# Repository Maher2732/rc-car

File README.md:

# RC Car

An autonomous-assist RC car built on three networked computers. You drive it with an Xbox controller paired straight to an ESP32 over Bluetooth. A Raspberry Pi watches the road with a 360° lidar and steps in when you're about to hit something. A second ESP32 watches the battery and runs a 3.5" dashboard display. Both ESP32s live on one custom mainboard (see [`PCB/`](PCB/)). All three talk over a CAN bus, the same kind of network real cars use.

```
                    Bluetooth (Bluepad32)
  Xbox controller  ─────────────────────►  ┌──────────────────────┐ ──PWM──► Steering servo
                                           │  DRIVE NODE (ESP32)  │
                                           │  steering + motor    │ ──PWM──► BTS7960 ──► Motor
                                           └──────────┬───────────┘
                                                      │
  ════════════════════════════ CAN bus, 500 kbit/s ═══╪══════════════════════════════
            │                                         │
  ┌─────────┴──────────────┐            ┌─────────────┴─────────┐
  │  RASPBERRY PI          │            │  TELEMETRY NODE       │ ──► 3.5" ILI9488 display
  │  lidar obstacle        │            │  (ESP32)              │ ◄── Battery voltage divider
  │  avoidance             │            │  battery + dashboard  │
  └─────────┬──────────────┘            └───────────────────────┘
            ▲
         RPLidar
```

## How It Works

1. **You drive.** The drive node reads the controller over Bluetooth and drives the steering servo and the motor through a BTS7960 H-bridge. No PC and no cables.
2. **The telemetry node reports.** It reads the battery voltage and broadcasts it on the CAN bus, and its display shows whether the controller is connected, battery %, and the nearest object the lidar sees.
3. **The Pi watches.** Every lidar scan, it looks for anything inside the corridor the car is about to drive through. It works out a stopping distance from the car's speed. There's no wheel-speed sensor, so it assumes a safe upper bound.
4. **The Pi corrects.** It sends a correction addressed to the drive node (CAN ID `0x100`) at 20 Hz: a throttle limit, a steering nudge toward the side with more room, or a full forward block. The drive node merges this with your input. You stay in control, and the car just won't let you drive into a wall.

## Engineering Highlights

- **Fail-safe by default.** Every link has a timeout, and losing one makes the car *more* cautious, never less:

  | Fault | Response |
  |-------|----------|
  | Controller disconnects | Neutral throttle, centered steering |
  | Pi stops sending (crash, unplugged, booting) | Forward throttle capped at 50% |
  | Lidar stops producing scans | Pi caps throttle at 30% |
  | Battery critically low | Throttle capped at 30%, latched until reboot |
  | CAN controller goes bus-off | Automatic recovery |

- **Speed-aware braking.** Stop distance = buffer + speed × reaction time + speed² / (2 × deceleration), with hysteresis so the block doesn't chatter at the threshold.
- **Shared protocol, checked in CI.** The CAN message layout lives in one C header. A Python test parses that header and fails if the Pi's copy drifts.
- **Pure, testable logic.** The rules for merging driver input with corrections (`drive_logic.c`) and the avoidance algorithm (`avoidance.py`) contain no hardware calls. The avoidance code has unit tests.
- **Drivetrain protection.** Throttle can only rise at a limited rate, which protects the 3D-printed differential from shock loads. Letting off and braking still take effect instantly.
- **Motor protection.** The H-bridge brakes for 250 ms before it reverses, so a full-speed forward-to-reverse flip never slams the spinning motor into reverse (a large current spike through the driver and the 3D-printed gears). Drag brake holds the crawler on slopes and stops it fast when the Pi cuts throttle. 20 kHz PWM keeps the motor quiet.
- **Haptic feedback.** The controller rumbles when the Pi blocks forward motion.
- **Real-time structure.** On the drive node, Bluetooth runs on core 0 and the 50 Hz control loop is pinned to core 1.

## Controls

| Input | Action |
|-------|--------|
| Left stick X | Steering |
| Right trigger | Throttle |
| Left trigger | Brake / reverse |
| Y | Toggle slow (40%) / fast (100%) mode |
| D-pad left / right | Steering trim (±1° per press) |

**Pairing:** power on the drive node, then hold the pair button on top of the Xbox controller until the logo flashes quickly. After the first pairing, the controller reconnects automatically. Only one controller can connect at a time. To forget the pairing, run `idf.py erase-flash` and reflash.

## Hardware

| Part | Notes |
|------|-------|
| 2× ESP32 dev board | Classic ESP32 (needs Bluetooth Classic + BLE for Xbox controllers) |
| Raspberry Pi | Any model with SPI; runs Raspberry Pi OS |
| 3× CAN transceiver | SN65HVD230 for each ESP32; MCP2515 CAN HAT for the Pi |
| Slamtec RPLIDAR A1M8 | 360°, 12 m range, USB to the Pi |
| 270° steering servo | 500–2500 µs pulse range |
| INJORA 540 35T brushed motor | Crawler motor, runs straight off the 2S pack |
| Treedix BTS7960 (43 A) | H-bridge motor driver, 20 kHz PWM |
| 5–6 V 7 A UBEC | Set to 5 V; powers the servo and both ESP32s from the LiPo (the BTS7960 has no BEC) |
| 3.5" ILI9488 SPI display (480×320, touch) | Dashboard on the telemetry ESP32 |
| RC Car Mainboard | Custom PCB carrying both ESP32s, CAN, power and connectors ([`PCB/`](PCB/)) |
| Zeee 2S 7.4 V 2200 mAh LiPo | Voltage measured through a 100k / 33k divider |
| Xbox Wireless Controller | Paired over Bluetooth |

### Wiring

**Drive node**

| ESP32 pin | Connects to |
|-----------|-------------|
| GPIO 18 | Steering servo signal |
| GPIO 25 | BTS7960 RPWM (forward) |
| GPIO 26 | BTS7960 LPWM (reverse) |
| GPIO 33 | BTS7960 R_EN + L_EN (tied together) |
| 3V3 | BTS7960 VCC (logic supply, see below) |
| GPIO 4 | CAN transceiver TX |
| GPIO 5 | CAN transceiver RX |

**Telemetry node**

| ESP32 pin | Connects to |
|-----------|-------------|
| GPIO 34 | Battery divider midpoint |
| GPIO 18 / 23 / 19 | Display SPI clock / MOSI / MISO (touch) |
| GPIO 13 / 21 / 22 | Display CS / DC / RESET |
| GPIO 32 | Display backlight (low = on, via a MOSFET on the mainboard) |
| GPIO 14 / 35 | Touch CS / IRQ (wired, not used yet) |
| GPIO 4 | CAN transceiver TX |
| GPIO 5 | CAN transceiver RX |

CAN pins default to GPIO 4 / 5 and can be changed in menuconfig.

**CAN bus:** connect CANH to CANH and CANL to CANL on all three transceivers, put a **120 Ω terminator at each end** of the bus, and share a common ground. Power the servo from a separate 5–6 V UBEC, not from the ESP32.

**BTS7960:** connect B+ / B− to the LiPo and M+ / M− to the motor. Power its **VCC from the ESP32's 3.3 V**, not 5 V. Its input buffer then treats the ESP32's 3.3 V signals as a clean logic high; at 5 V they're borderline. Leave R_IS / L_IS unconnected.

### Power

```
                ┌──► BTS7960 B+/B− ──► Motor
2S LiPo 7.4 V ──┼──► UBEC (5 V) ──┬──► Steering servo (+/−)
                │                 ├──► Drive ESP32 (5V/VIN pin)
                │                 └──► Telemetry ESP32 (5V/VIN pin)
                └──► Telemetry battery divider (100k / 33k)

Raspberry Pi: its own 5 V 3 A+ supply (power bank or a second buck converter)
```

- **Set the UBEC to 5 V.** The ESP32 boards expect 5 V on their 5V/VIN pin, and most hobby servos are happy at 5 V. If your servo is rated for 6 V you'll get a bit more speed and torque at 6 V, but then power the ESP32s separately.
- **Keep the Raspberry Pi off the servo's supply.** A servo straining under load pulls amps in bursts and drags the rail down, which can make the Pi brown out and corrupt its SD card. A Pi 4 alone wants 5 V / 3 A.
- **Common ground.** Every negative wire (LiPo, UBEC, BTS7960, both ESP32s, Pi, CAN transceivers) must connect, or PWM and CAN signals have no reference.
- **Don't plug in USB and the UBEC at once** on an ESP32 unless your board has a protection diode on its 5V pin.

## CAN Protocol

Classic CAN at 500 kbit/s, 11-bit IDs, little-endian. Full definition: [`rc_can_protocol.h`](firmware/components/rc_common/include/rc_can_protocol.h).

| ID | From → To | Rate | Contents |
|----|-----------|------|----------|
| `0x100` | Pi → Drive (+ telemetry display) | 20 Hz | Steering offset, throttle limit, block-forward flag, nearest obstacle in the path and in any direction |
| `0x200` | Drive → all | 20 Hz | Steering angle, throttle, status flags |
| `0x300` | (reserved) | | Wheel speed, for a future speed sensor |
| `0x301` | Telemetry → all | 5 Hz | Pack voltage, % charge, low/critical flags |

Each message carries a rolling counter, and receivers treat a message older than 300 ms as "node offline".

## Getting Started

### 1. Clone with submodules

Bluepad32 and BTstack are git submodules:

```bash
git clone --recursive https://github.com/Maher2732/rc-car.git
```

If you already cloned without `--recursive`:

```bash
git submodule update --init --recursive
```

### 2. Flash the ESP32s

Requires [ESP-IDF](https://docs.espressif.com/projects/esp-idf/) v6.1. Every ESP32 runs the same firmware project; you pick what each board does in menuconfig:

```bash
cd firmware
idf.py menuconfig
```

Go to **RC Car Configuration → Board role** and choose one:

| Role | What it does |
|------|--------------|
| Drive node *(default)* | Xbox controller over Bluetooth, steering servo, BTS7960 motor driver, applies Pi corrections |
| Telemetry node | Battery monitoring and the dashboard display |
| CAN sender | Test tool: sends a frame every second |
| CAN receiver | Test tool: listen-only, prints every frame on the bus |

Then build and flash:

```bash
idf.py build flash monitor
```

Changing role rewrites `sdkconfig`, so flash one board, change the role, and flash the next. The CAN sender/receiver roles are handy for checking the wiring and termination before running the real nodes.

Tune pins, steering limits, speed modes and battery settings in `main/drive/config.h` and `main/telemetry/config.h`.

### 3. Set up the Raspberry Pi

Enable the CAN HAT in `/boot/firmware/config.txt`. Match `oscillator` to the crystal on your HAT:

```
dtparam=spi=on
dtoverlay=mcp2515-can0,oscillator=8000000,interrupt=25
```

Bring `can0` up at boot and install the code:

```bash
sudo cp pi/deploy/can0.network /etc/systemd/network/80-can0.network
sudo systemctl enable --now systemd-networkd
cd pi && python3 -m venv .venv && .venv/bin/pip install -r requirements.txt
```

Run it by hand:

```bash
.venv/bin/python -m rc_pi.main --lidar-port /dev/ttyUSB0 --verbose
```

Or install it as a service that starts at boot:

```bash
sudo cp deploy/rc-pi.service /etc/systemd/system/ && sudo systemctl enable --now rc-pi
```

Tune car width, braking deceleration and lidar mounting angle in [`pi/rc_pi/config.py`](pi/rc_pi/config.py).

### 4. Run the tests

```bash
cd pi && python -m unittest discover -s tests -t . -v
```

GitHub Actions runs these tests and builds the firmware in every board role on every push.

## Project Structure

```
firmware/                      # One ESP-IDF project, board role chosen in menuconfig
├── main/
│   ├── main.c                 #   Runs the selected role
│   ├── Kconfig.projbuild      #   Board role + CAN pins
│   ├── drive/                 #   Role: drive node
│   │   ├── gamepad.c          #     Bluepad32 platform: Xbox controller input
│   │   ├── drive_logic.c      #     Merges driver input with Pi corrections and limits
│   │   ├── actuators.c        #     Servo PWM + BTS7960 motor driver
│   │   └── config.h           #     Pins and tuning
│   ├── telemetry/             #   Role: telemetry node
│   │   ├── display.c          #     ILI9488 driver + 5x7 font
│   │   ├── telemetry_node.c   #     Battery messages + dashboard screen
│   │   ├── battery.c          #     Calibrated ADC, LiPo charge estimate, low/critical flags
│   │   └── config.h
│   ├── can_sender.c           #   Role: CAN test sender
│   └── can_receiver.c         #   Role: CAN test receiver
├── components/rc_common/      # Shared CAN driver + protocol header
└── external/bluepad32/        # Submodule
pi/
├── rc_pi/
│   ├── avoidance.py           # Obstacle detection + correction logic
│   ├── lidar.py               # Background RPLidar reader with auto-reconnect
│   ├── can_link.py            # CAN send/receive
│   ├── protocol.py            # Python mirror of the CAN protocol
│   └── main.py                # 20 Hz main loop
├── tests/                     # Unit tests (avoidance, protocol sync, CAN link)
└── deploy/                    # systemd service + CAN interface config
PCB/
├── generator/                 # Python that generates the KiCad schematic + board
├── mainboard/                 # KiCad 10 project
├── fab/                       # Gerbers, BOM, pick-and-place for PCBWay
└── images/                    # 3D renders
```

## Roadmap

- [ ] Block reverse when the lidar sees something behind the car
- [ ] Log CAN traffic on the Pi for replay and tuning
- [ ] Use the display's touch panel (speed mode, steering trim)
- [ ] Wheel-speed sensor for tighter braking distances

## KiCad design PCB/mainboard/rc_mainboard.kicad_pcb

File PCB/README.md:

# RC Car Mainboard

One board that replaces the wiring nest: both ESP32s, CAN, power, and every connector the car needs. The Raspberry Pi stays on its own board and joins over the CAN connector.

| | |
|---|---|
| Size | **130 × 100 mm** (5.1 × 3.9 in), 3 mm corner radius |
| Layers | 2, 1.6 mm FR-4 |
| Copper | 2 oz recommended (battery → motor path carries motor current) |
| Smallest features | 0.15 mm traces, 0.2 mm holes (PCBWay standard process) |

## What's on it

| Block | Parts |
|-------|-------|
| Power input | XT60 battery in, 30 A blade fuse, reverse-polarity MOSFET, soft on/off switch (MOSFET + edge slide switch), XT60 out to the BTS7960 |
| Servo supply | TPS54560B, 5 V / 5 A, own polyfuse |
| Logic supply | AP63205 5 V buck, OR-ed with both USB ports, AMS1117 3.3 V |
| Drive ESP32 | ESP32-WROOM-32E, USB-C + CH340C with auto-program, servo header, 8-pin BTS7960 header |
| Telemetry ESP32 | ESP32-WROOM-32E, USB-C + CH340C, battery voltage divider, 14-pin display socket |
| CAN | Two SN65HVD230 on board, split 120 Ω termination (cut JP1 to disable), TVS protection, JST-XH to the Pi |

### Connectors

| Ref | Connector | Goes to |
|-----|-----------|---------|
| J1 | XT60 male | 2S LiPo |
| J2 | XT60 female | BTS7960 B+ / B− |
| SW1 | Slide switch (board edge) | Turns the whole car on and off |
| J6 | 1×8 header, 2.54 mm | BTS7960 control header, pin for pin (straight ribbon) |
| J7 | 1×3 header, 2.54 mm | Steering servo (S, +, −) |
| J8 | 1×14 socket, 2.54 mm | 3.5" ILI9488 display, pin for pin |
| J5 | JST-XH 3-pin | CAN to the Raspberry Pi (H, L, GND) |
| J3 / J4 | USB-C | Flash / power the drive / telemetry ESP32 |

## Ordering from PCBWay

Upload `fab/rc_mainboard_gerbers.zip` at pcbway.com → PCB Instant Quote → Quick-order PCB. Settings:

| Option | Value |
|--------|-------|
| Layers | 2 |
| Size | 130 × 100 mm |
| Thickness | 1.6 mm |
| Min track / spacing | 6/6 mil (0.15 mm) |
| Min hole | 0.2 mm |
| Outer copper | **2 oz** |
| Surface finish | HASL lead-free (or ENIG) |

**Assembly (optional):** choose PCB Assembly and upload `fab/rc_mainboard_bom.csv` and `fab/rc_mainboard_centroid.csv` with the Gerbers. The BOM lists a manufacturer part number for every IC, so PCBWay can source them. Through-hole parts (XT60s, fuse holder, switch, headers) are marked THT; they're easy to hand-solder if you'd rather save on assembly.

The ESP32 modules ship blank. Flash each one over its own USB-C port; pick the role in `idf.py menuconfig` (drive on the board marked USB DRIVE, telemetry on USB TELEMETRY).

## Before you power it up

1. Inspect the battery path (J1 → F1 → Q1 → Q2 → J2) for solder bridges.
2. Plug in USB only first: the green power LED should light and both ESP32s should enumerate.
3. Then connect the battery with SW1 off, and turn SW1 on.
4. Check the servo rail (J7 pin 2) reads about 5.0 V before plugging the servo in.

## Design notes

- **Servo supply compensation** uses values for a 5 V / 5 A output at ~490 kHz. They're a reasonable starting point; confirm with TI's WEBENCH or the TPS54560B datasheet before ordering a large batch.
- **Antennas** overhang the top edge with a copper keep-out underneath; mount the board so nothing metal sits right above them.
- **Display backlight** is switched by Q7: IO32 low = on (the firmware does this).
- **Touch panel** is wired (SPI shared with the display, IO14 CS, IO35 IRQ) but the firmware doesn't use it yet.

## Regenerating

Everything is generated from [`generator/design.py`](generator/design.py), one list of every part and connection. Edit that, not the KiCad files.

```bash
cd PCB/generator
python gen_sch.py                      # schematic
<kicad>/bin/python.exe route.py        # board + autoroute (needs Freerouting + Java 25)
<kicad>/bin/python.exe export.py       # PCBWay files + renders
```

`<kicad>` is the KiCad 10 install folder; `route.py` reads `FREEROUTING_JAR` and `JAVA` from the environment.

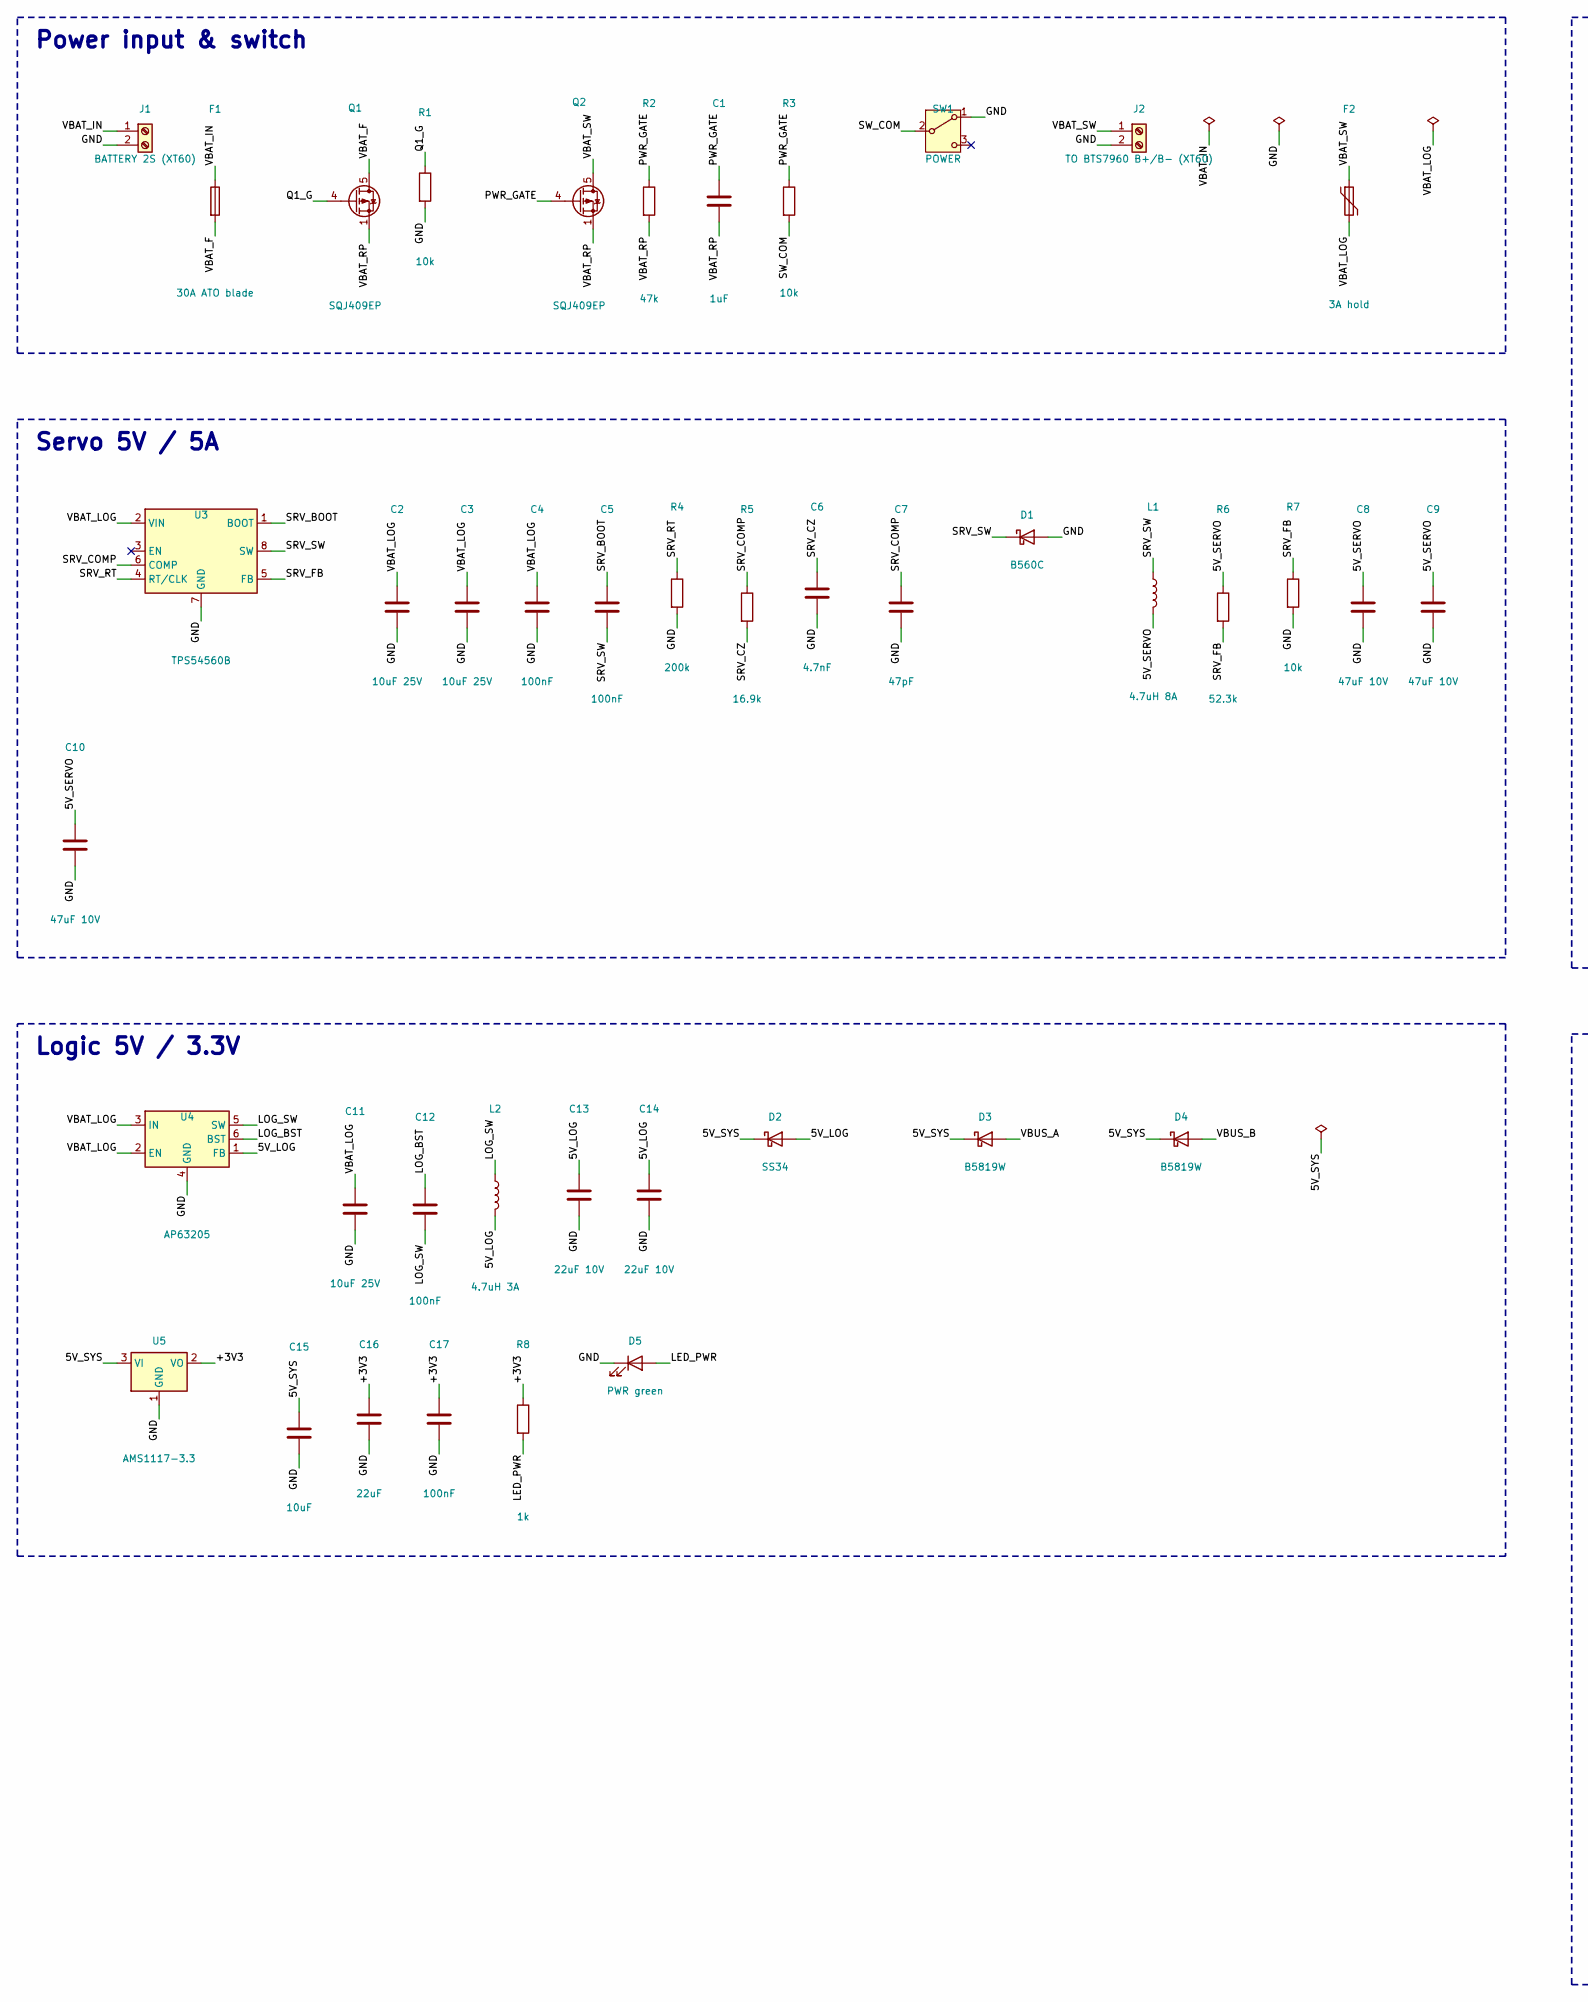
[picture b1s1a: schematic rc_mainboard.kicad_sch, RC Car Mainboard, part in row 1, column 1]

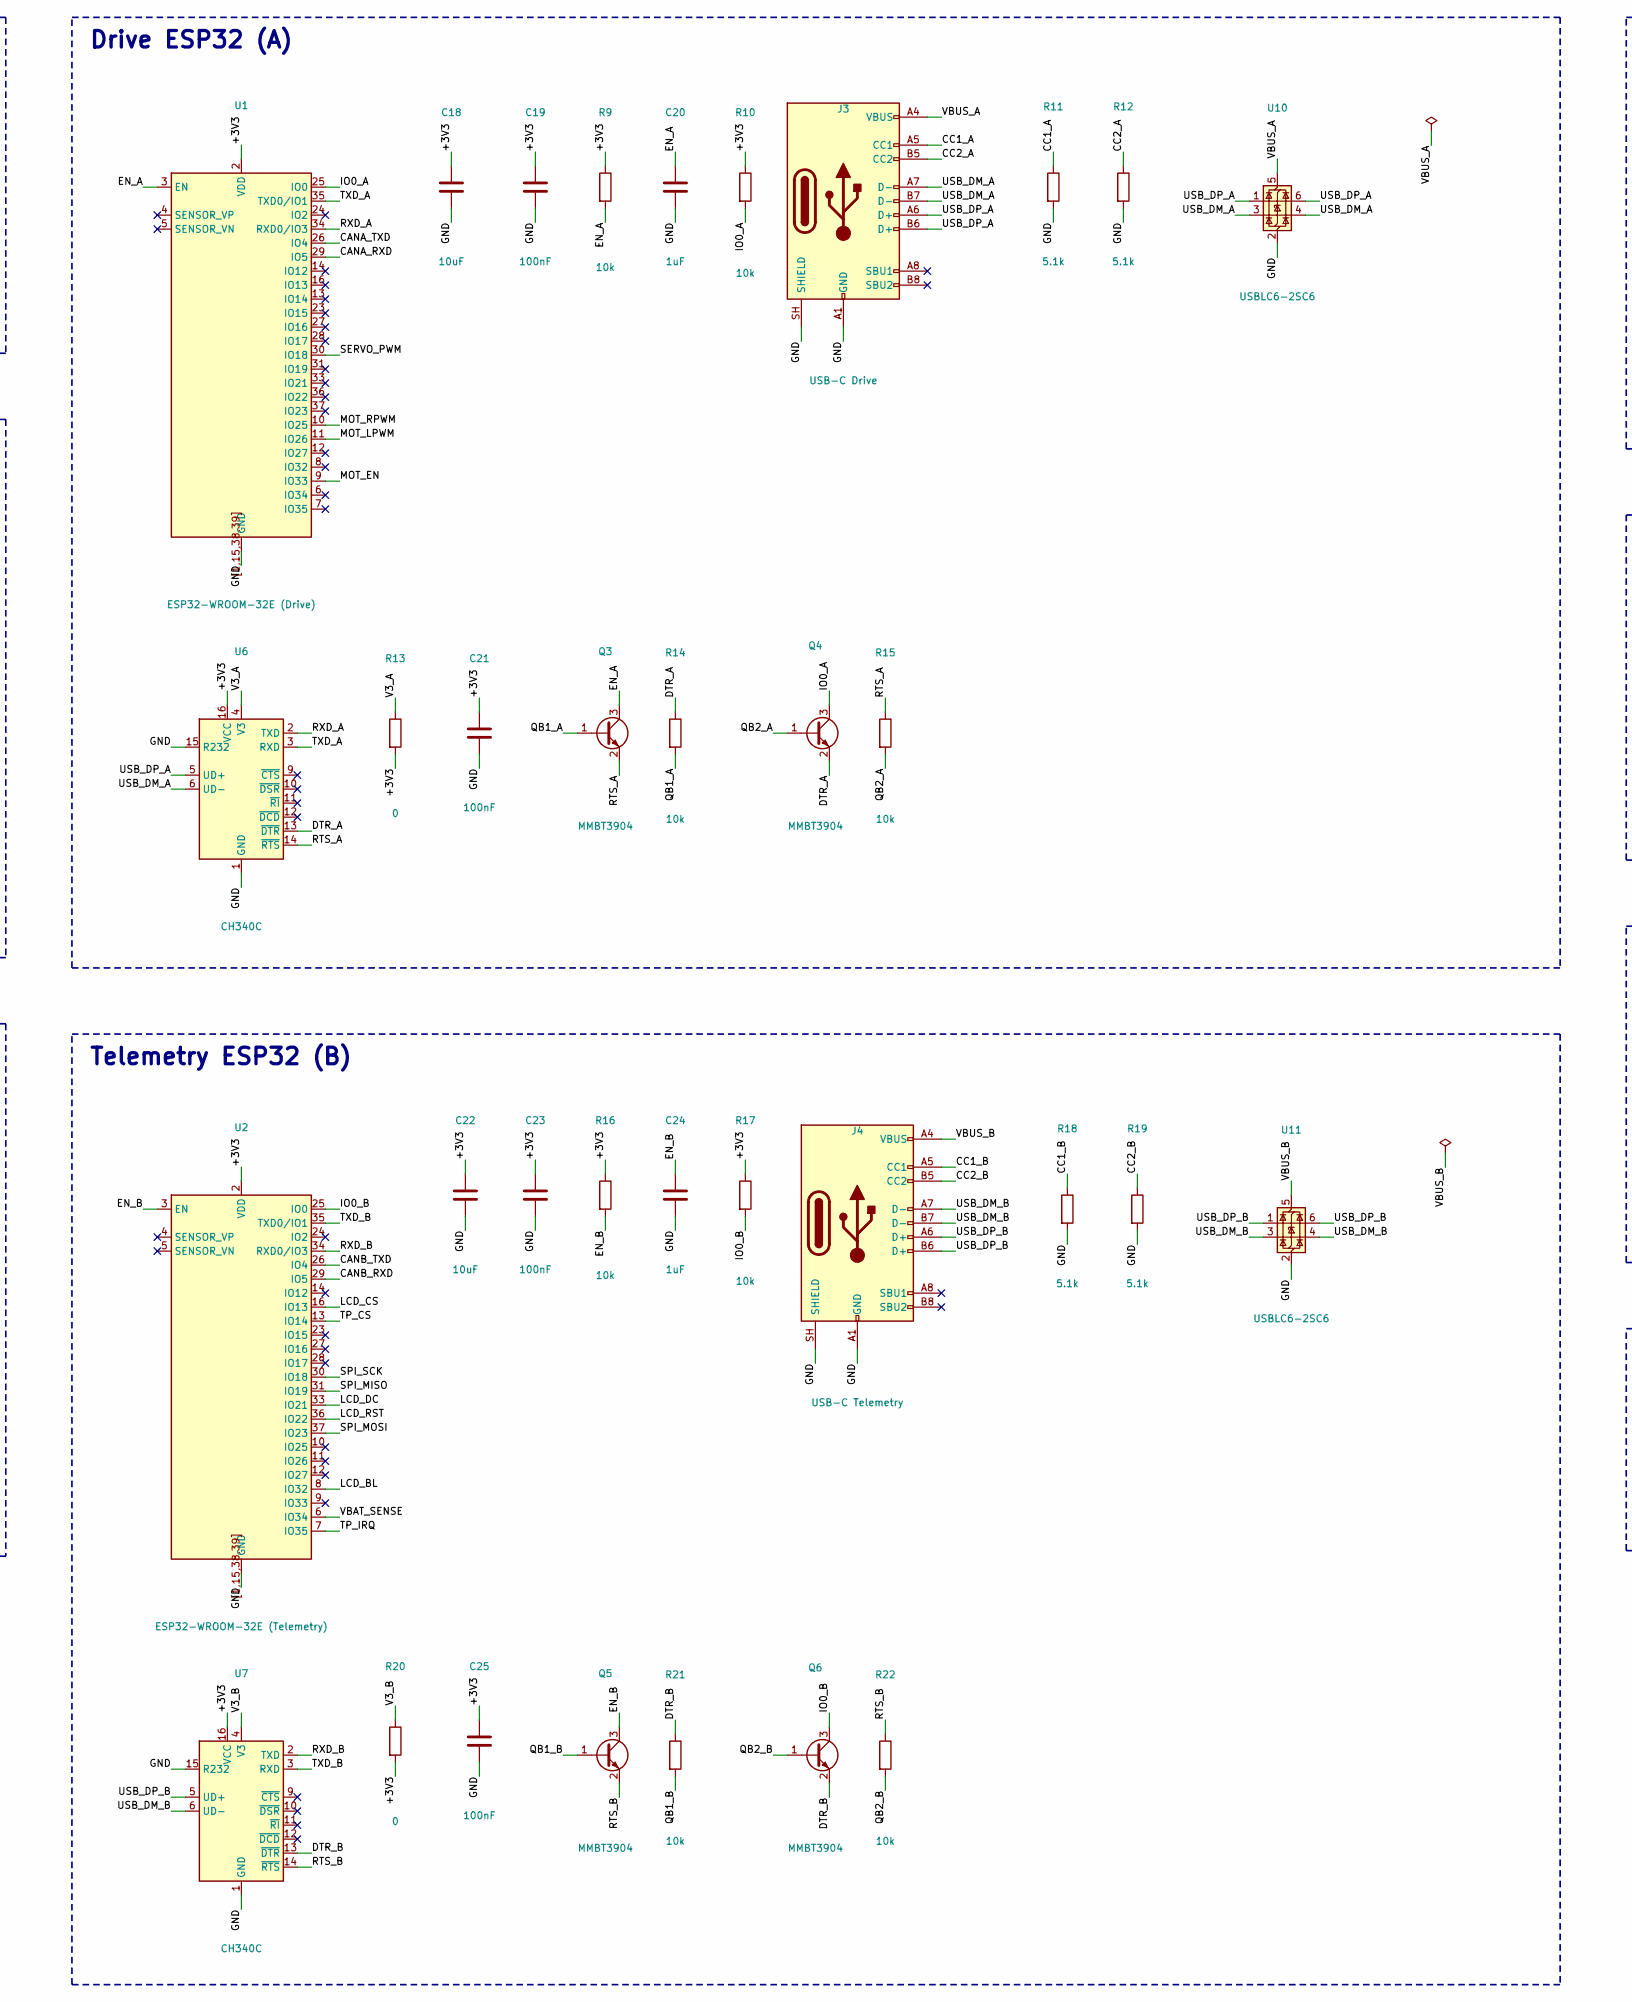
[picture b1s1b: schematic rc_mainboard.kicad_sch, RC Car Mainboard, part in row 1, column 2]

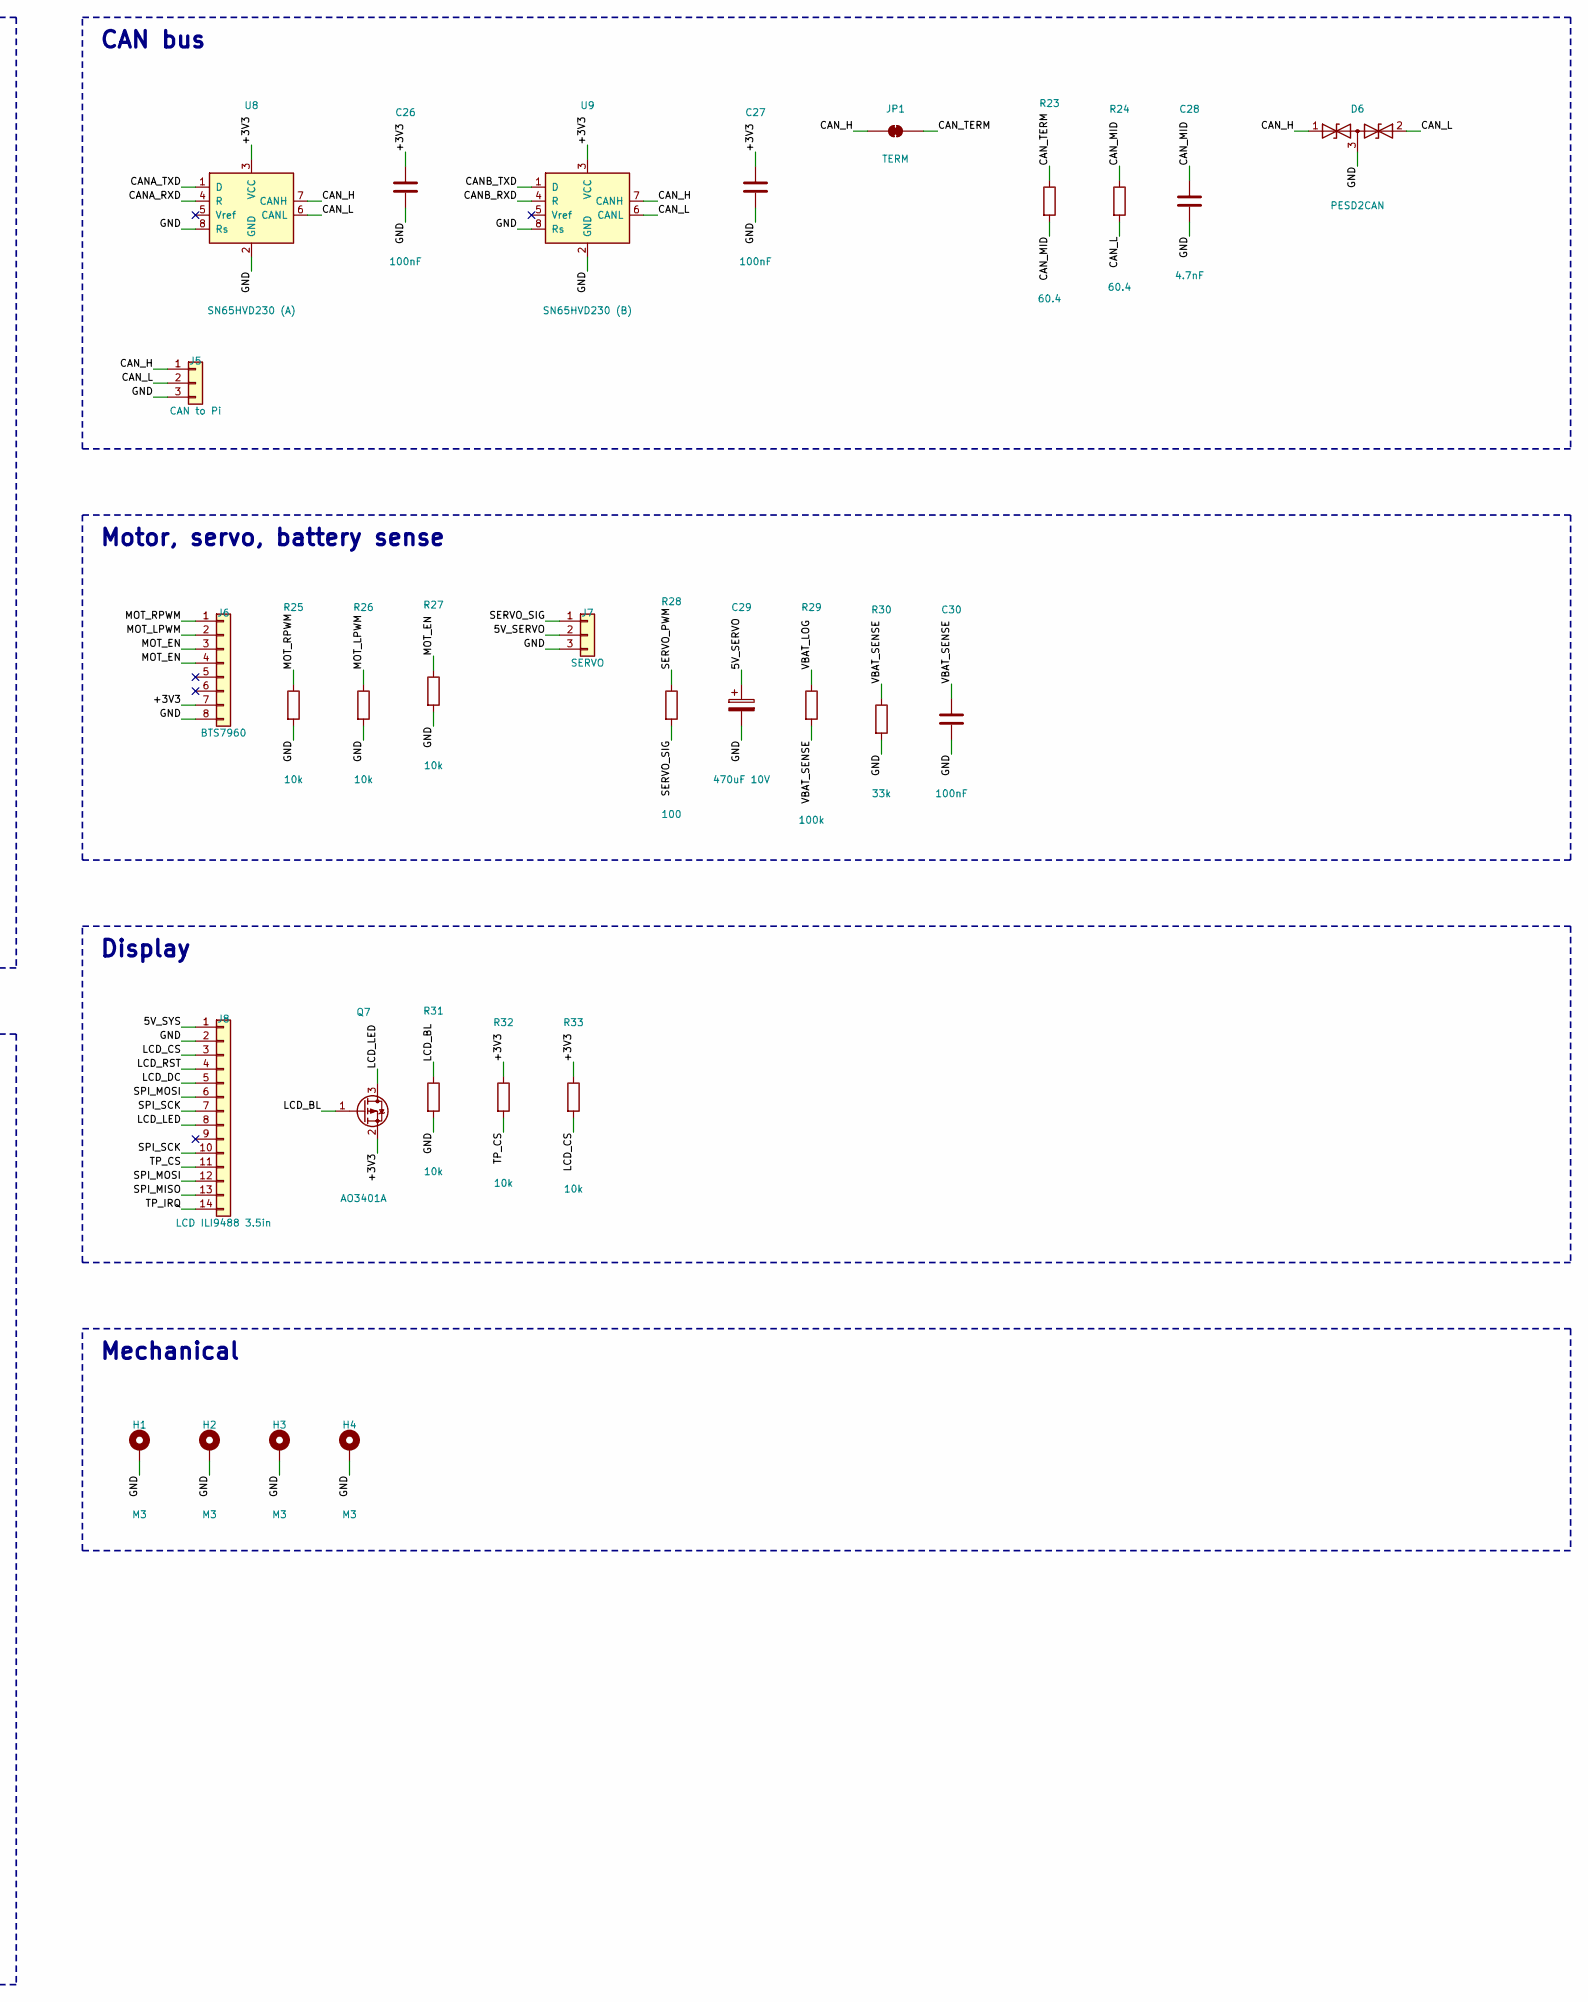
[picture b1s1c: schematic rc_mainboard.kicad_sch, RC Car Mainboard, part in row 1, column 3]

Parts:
C1: 1uF; C_0805_2012Metric
C2, C3, C11: 10uF 25V; C_1206_3216Metric
C4, C5, C12, C17, C19, C21, C23, C25, C26, C27, C30: 100nF; C_0603_1608Metric
C6, C28: 4.7nF; C_0603_1608Metric
C7: 47pF; C_0603_1608Metric
C8, C9, C10: 47uF 10V; C_1206_3216Metric
C13, C14: 22uF 10V; C_0805_2012Metric
C15, C18, C22: 10uF; C_0805_2012Metric
C16: 22uF; C_0805_2012Metric
C20, C24: 1uF; C_0603_1608Metric
C29: 470uF 10V; CP_Elec_8x10
D1: B560C; D_SMC; MPN B560C-13-F
D2: SS34; D_SMA; MPN SS34
D3, D4: B5819W; D_SOD-123; MPN B5819W
D5: PWR green; LED_0603_1608Metric
D6: PESD2CAN; SOT-23; MPN PESD2CAN,215
F1: 30A ATO blade; FuseHolder_Blade_ATO_Littelfuse_FLR_178.6165; MPN Littelfuse 178.6165
F2: 3A hold; Fuse_2920_7451Metric; MPN PTC 2920 3A hold
H1, H2, H3, H4: M3; MountingHole_3.2mm_M3_Pad_Via
J1: BATTERY 2S (XT60); AMASS_XT60PW-M_1x02_P7.20mm_Horizontal; MPN XT60PW-M
J2: TO BTS7960 B+/B- (XT60); AMASS_XT60PW-F_1x02_P7.20mm_Horizontal; MPN XT60PW-F
J3: USB-C Drive; USB_C_Receptacle_HRO_TYPE-C-31-M-12; MPN TYPE-C-31-M-12
J4: USB-C Telemetry; USB_C_Receptacle_HRO_TYPE-C-31-M-12; MPN TYPE-C-31-M-12
J5: CAN to Pi; JST_XH_B3B-XH-A_1x03_P2.50mm_Vertical; MPN B3B-XH-A
J6: BTS7960; PinHeader_1x08_P2.54mm_Vertical
J7: SERVO; PinHeader_1x03_P2.54mm_Vertical
J8: LCD ILI9488 3.5in; PinSocket_1x14_P2.54mm_Vertical
JP1: TERM; SolderJumper-2_P1.3mm_Bridged_RoundedPad1.0x1.5mm
L1: 4.7uH 8A; L_Bourns_SRP1038C_10.0x10.0mm; MPN SRP1038C-4R7M
L2: 4.7uH 3A; L_Bourns-SRN4018; MPN SRN4018-4R7M
Q1, Q2: SQJ409EP; PowerPAK_SO-8L_Single; MPN SQJ409EP-T1_GE3
Q3, Q4, Q5, Q6: MMBT3904; SOT-23; MPN MMBT3904
Q7: AO3401A; SOT-23; MPN AO3401A
R1, R3, R7, R9, R10, R14, R15, R16, R17, R21, R22, R25, R26, R27, R31, R32, R33: 10k; R_0603_1608Metric
R2: 47k; R_0603_1608Metric
R4: 200k; R_0603_1608Metric
R5: 16.9k; R_0603_1608Metric
R6: 52.3k; R_0603_1608Metric
R8: 1k; R_0603_1608Metric
R11, R12, R18, R19: 5.1k; R_0603_1608Metric
R13, R20: 0; R_0603_1608Metric
R23, R24: 60.4; R_0603_1608Metric
R28: 100; R_0603_1608Metric
R29: 100k; R_0603_1608Metric
R30: 33k; R_0603_1608Metric
SW1: POWER; SW_Slide_SPDT_Angled_CK_OS102011MA1Q; MPN OS102011MA1QN1
U1: ESP32-WROOM-32E (Drive); ESP32-WROOM-32E; MPN ESP32-WROOM-32E-N4
U2: ESP32-WROOM-32E (Telemetry); ESP32-WROOM-32E; MPN ESP32-WROOM-32E-N4
U3: TPS54560B; Texas_R-PDSO-G8_EP2.95x4.9mm_Mask2.4x3.1mm_ThermalVias; MPN TPS54560BDDAR
U4: AP63205; TSOT-23-6; MPN AP63205WU-7
U5: AMS1117-3.3; SOT-223-3_TabPin2; MPN AMS1117-3.3
U6, U7: CH340C; SOIC-16_3.9x9.9mm_P1.27mm; MPN CH340C
U8: SN65HVD230 (A); SOIC-8_3.9x4.9mm_P1.27mm; MPN SN65HVD230DR
U9: SN65HVD230 (B); SOIC-8_3.9x4.9mm_P1.27mm; MPN SN65HVD230DR
U10, U11: USBLC6-2SC6; SOT-23-6; MPN USBLC6-2SC6

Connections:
/5V_LOG: C13.1, C14.1, D2.2 (A), L2.2, U4.1 (FB)
/5V_SERVO: C8.1, C9.1, C10.1, C29.1, J7.2, L1.2, R6.1
/5V_SYS: C15.1, D2.1 (K), D3.1 (K), D4.1 (K), J8.1, U5.3 (VI)
/+3V3: C16.1, C17.1, C18.1, C19.1, C21.1, C22.1, C23.1, C25.1, C26.1, C27.1, J6.7, Q7.2 (S), R8.1, R9.1, R10.1, R13.2, R16.1, R17.1, R20.2, R32.1, R33.1, U1.2 (VDD), U2.2 (VDD), U5.2 (VO), U6.16 (VCC), U7.16 (VCC), U8.3 (VCC), U9.3 (VCC)
/CANA_RXD: U1.29 (IO5), U8.4 (R)
/CANA_TXD: U1.26 (IO4), U8.1 (D)
/CANB_RXD: U2.29 (IO5), U9.4 (R)
/CANB_TXD: U2.26 (IO4), U9.1 (D)
/CAN_H: D6.1 (A1), J5.1, JP1.1 (A), U8.7 (CANH), U9.7 (CANH)
/CAN_L: D6.2 (A2), J5.2, R24.2, U8.6 (CANL), U9.6 (CANL)
/CAN_MID: C28.1, R23.2, R24.1
/CAN_TERM: JP1.2 (B), R23.1
/CC1_A: J3.A5 (CC1), R11.1
/CC1_B: J4.A5 (CC1), R18.1
/CC2_A: J3.B5 (CC2), R12.1
/CC2_B: J4.B5 (CC2), R19.1
/DTR_A: Q4.2 (E), R14.1, U6.13 (~DTR)
/DTR_B: Q6.2 (E), R21.1, U7.13 (~DTR)
/EN_A: C20.1, Q3.3 (C), R9.2, U1.3 (EN)
/EN_B: C24.1, Q5.3 (C), R16.2, U2.3 (EN)
/GND: C2.2, C3.2, C4.2, C6.2, C7.2, C8.2, C9.2, C10.2, C11.2, C13.2, C14.2, C15.2, C16.2, C17.2, C18.2, C19.2, C20.2, C21.2, C22.2, C23.2, C24.2, C25.2, C26.2, C27.2, C28.2, C29.2, C30.2, D1.2 (A), D5.1 (K), D6.3 (common), H1.1, H2.1, H3.1, H4.1, J1.2, J2.2, J3.A1 (GND), J3.A12 (GND), J3.B1 (GND), J3.B12 (GND), J3.SH (SHIELD), J4.A1 (GND), J4.A12 (GND), J4.B1 (GND), J4.B12 (GND), J4.SH (SHIELD), J5.3, J6.8, J7.3, J8.2, R1.2, R4.2, R7.2, R11.2, R12.2, R18.2, R19.2, R25.2, R26.2, R27.2, R30.2, R31.2, SW1.1 (A), U1.1, U1.15, U1.38, U1.39, U1.[1,15,38,39] (GND), U2.1, U2.15, U2.38, U2.39, U2.[1,15,38,39] (GND), U3.7 (GND), U3.9 (GND), U4.4 (GND), U5.1 (GND), U6.1 (GND), U6.15 (R232), U7.1 (GND), U7.15 (R232), U8.2 (GND), U8.8 (Rs), U9.2 (GND), U9.8 (Rs), U10.2 (GND), U11.2 (GND)
/IO0_A: Q4.3 (C), R10.2, U1.25 (IO0)
/IO0_B: Q6.3 (C), R17.2, U2.25 (IO0)
/LCD_BL: Q7.1 (G), R31.1, U2.8 (IO32)
/LCD_CS: J8.3, R33.2, U2.16 (IO13)
/LCD_DC: J8.5, U2.33 (IO21)
/LCD_LED: J8.8, Q7.3 (D)
/LCD_RST: J8.4, U2.36 (IO22)
/LED_PWR: D5.2 (A), R8.2
/LOG_BST: C12.1, U4.6 (BST)
/LOG_SW: C12.2, L2.1, U4.5 (SW)
/MOT_EN: J6.3, J6.4, R27.1, U1.9 (IO33)
/MOT_LPWM: J6.2, R26.1, U1.11 (IO26)
/MOT_RPWM: J6.1, R25.1, U1.10 (IO25)
/PWR_GATE: C1.1, Q2.4 (G), R2.1, R3.1
/Q1_G: Q1.4 (G), R1.1
/QB1_A: Q3.1 (B), R14.2
/QB1_B: Q5.1 (B), R21.2
/QB2_A: Q4.1 (B), R15.2
/QB2_B: Q6.1 (B), R22.2
/RTS_A: Q3.2 (E), R15.1, U6.14 (~RTS)
/RTS_B: Q5.2 (E), R22.1, U7.14 (~RTS)
/RXD_A: U1.34 (RXD0/IO3), U6.2 (TXD)
/RXD_B: U2.34 (RXD0/IO3), U7.2 (TXD)
/SERVO_PWM: R28.1, U1.30 (IO18)
/SERVO_SIG: J7.1, R28.2
/SPI_MISO: J8.13, U2.31 (IO19)
/SPI_MOSI: J8.6, J8.12, U2.37 (IO23)
/SPI_SCK: J8.7, J8.10, U2.30 (IO18)
/SRV_BOOT: C5.1, U3.1 (BOOT)
/SRV_COMP: C7.1, R5.1, U3.6 (COMP)
/SRV_CZ: C6.1, R5.2
/SRV_FB: R6.2, R7.1, U3.5 (FB)
/SRV_RT: R4.1, U3.4 (RT/CLK)
/SRV_SW: C5.2, D1.1 (K), L1.1, U3.8 (SW)
/SW_COM: R3.2, SW1.2 (B)
/TP_CS: J8.11, R32.2, U2.13 (IO14)
/TP_IRQ: J8.14, U2.7 (IO35)
/TXD_A: U1.35 (TXD0/IO1), U6.3 (RXD)
/TXD_B: U2.35 (TXD0/IO1), U7.3 (RXD)
/USB_DM_A: J3.A7 (D-), J3.B7 (D-), U6.6 (UD-), U10.3 (I/O2), U10.4 (I/O2)
/USB_DM_B: J4.A7 (D-), J4.B7 (D-), U7.6 (UD-), U11.3 (I/O2), U11.4 (I/O2)
/USB_DP_A: J3.A6 (D+), J3.B6 (D+), U6.5 (UD+), U10.1 (I/O1), U10.6 (I/O1)
/USB_DP_B: J4.A6 (D+), J4.B6 (D+), U7.5 (UD+), U11.1 (I/O1), U11.6 (I/O1)
/V3_A: R13.1, U6.4 (V3)
/V3_B: R20.1, U7.4 (V3)
/VBAT_F: F1.2, Q1.5 (D)
/VBAT_IN: F1.1, J1.1
/VBAT_LOG: C2.1, C3.1, C4.1, C11.1, F2.2, R29.1, U3.2 (VIN), U4.2 (EN), U4.3 (IN)
/VBAT_RP: C1.2, Q1.1 (S), Q1.2 (S), Q1.3 (S), Q2.1 (S), Q2.2 (S), Q2.3 (S), R2.2
/VBAT_SENSE: C30.1, R29.2, R30.1, U2.6 (IO34)
/VBAT_SW: F2.1, J2.1, Q2.5 (D)
/VBUS_A: D3.2 (A), J3.A4 (VBUS), J3.A9 (VBUS), J3.B4 (VBUS), J3.B9 (VBUS), U10.5 (VBUS)
/VBUS_B: D4.2 (A), J4.A4 (VBUS), J4.A9 (VBUS), J4.B4 (VBUS), J4.B9 (VBUS), U11.5 (VBUS)

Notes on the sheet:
Power input & switch
Servo 5V / 5A
Logic 5V / 3.3V
Drive ESP32 (A)
Telemetry ESP32 (B)
CAN bus
Motor, servo, battery sense
Display
Mechanical

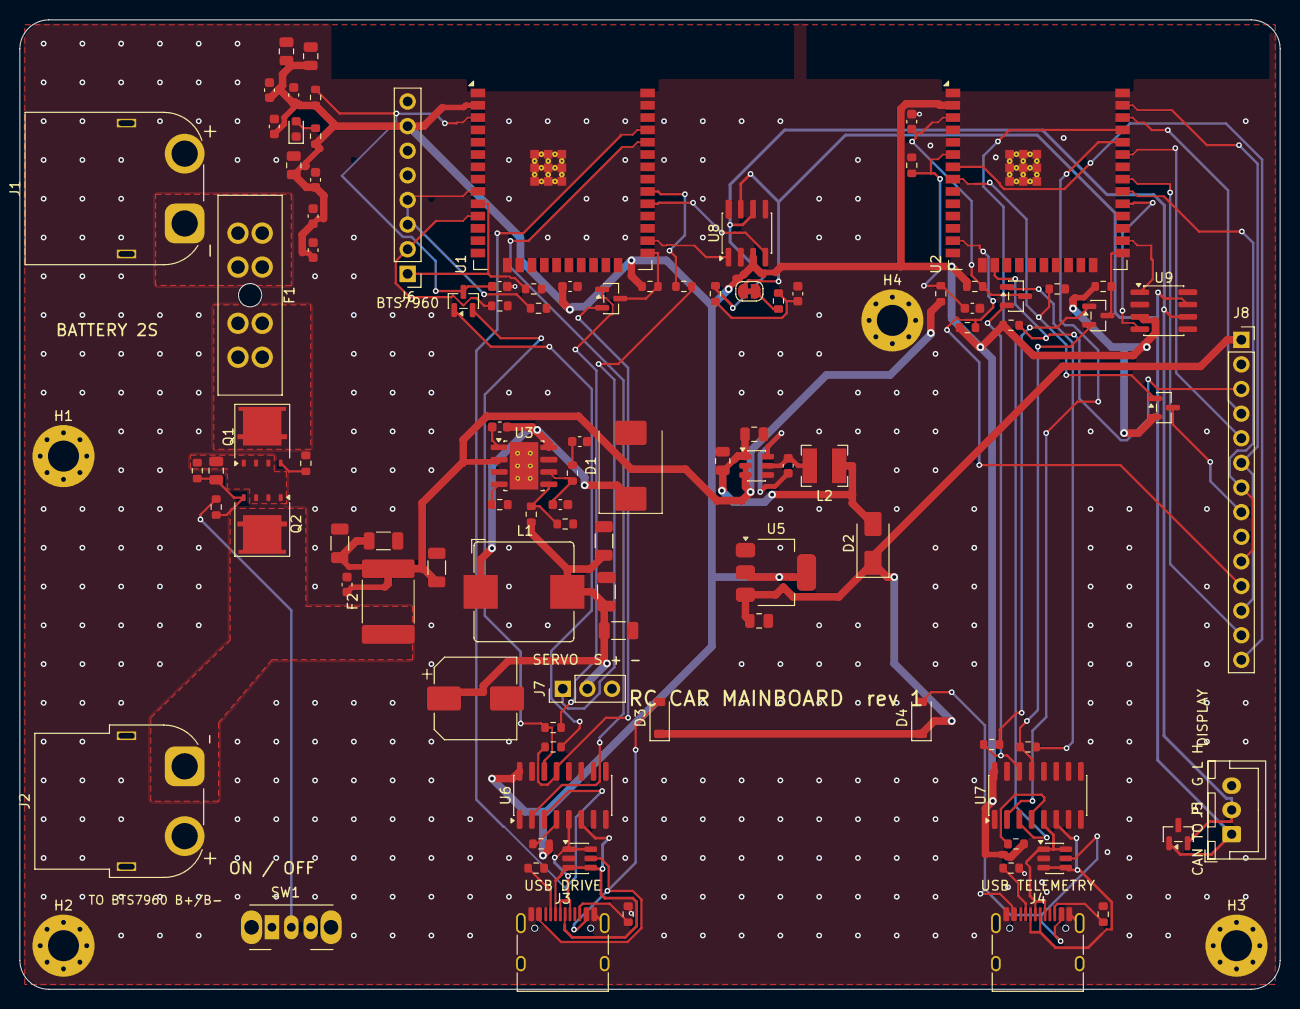
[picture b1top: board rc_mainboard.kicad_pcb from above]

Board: 2 copper layers, 130.0 x 100.0 mm, 105 parts (0 on the bottom side), 74 nets.

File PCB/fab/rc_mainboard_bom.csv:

Item #,Designator,Qty,Manufacturer,Mfg Part #,Description / Value,Package/Footprint,Type
1,J1,1,AMASS,XT60PW-M,BATTERY 2S (XT60),AMASS_XT60PW-M_1x02_P7.20mm_Horizontal,THT
2,F1,1,Littelfuse,Littelfuse 178.6165,30A ATO blade,FuseHolder_Blade_ATO_Littelfuse_FLR_178.6165,THT
3,"Q1,Q2",2,Vishay,SQJ409EP-T1_GE3,SQJ409EP,PowerPAK_SO-8L_Single,SMD
4,"R1,R3,R7,R9,R10,R14,R15,R16,R17,R21,R22,R25,R26,R27,R31,R32,R33",17,,,10k,R_0603_1608Metric,SMD
5,R2,1,,,47k,R_0603_1608Metric,SMD
6,C1,1,,,1uF,C_0805_2012Metric,SMD
7,SW1,1,C&K,OS102011MA1QN1,POWER,SW_Slide_SPDT_Angled_CK_OS102011MA1Q,THT
8,J2,1,AMASS,XT60PW-F,TO BTS7960 B+/B- (XT60),AMASS_XT60PW-F_1x02_P7.20mm_Horizontal,THT
9,F2,1,,PTC 2920 3A hold,3A hold,Fuse_2920_7451Metric,SMD
10,U3,1,Texas Instruments,TPS54560BDDAR,TPS54560B,Texas_R-PDSO-G8_EP2.95x4.9mm_Mask2.4x3.1mm_ThermalVias,SMD
11,"C2,C3,C11",3,,,10uF 25V,C_1206_3216Metric,SMD
12,"C4,C5,C12,C17,C19,C21,C23,C25,C26,C27,C30",11,,,100nF,C_0603_1608Metric,SMD
13,R4,1,,,200k,R_0603_1608Metric,SMD
14,R5,1,,,16.9k,R_0603_1608Metric,SMD
15,"C6,C28",2,,,4.7nF,C_0603_1608Metric,SMD
16,C7,1,,,47pF,C_0603_1608Metric,SMD
17,D1,1,Diodes Inc,B560C-13-F,B560C,D_SMC,SMD
18,L1,1,Bourns,SRP1038C-4R7M,4.7uH 8A,L_Bourns_SRP1038C_10.0x10.0mm,SMD
19,R6,1,,,52.3k,R_0603_1608Metric,SMD
20,"C8,C9,C10",3,,,47uF 10V,C_1206_3216Metric,SMD
21,U4,1,Diodes Inc,AP63205WU-7,AP63205,TSOT-23-6,SMD
22,L2,1,Bourns,SRN4018-4R7M,4.7uH 3A,L_Bourns-SRN4018,SMD
23,"C13,C14",2,,,22uF 10V,C_0805_2012Metric,SMD
24,D2,1,onsemi,SS34,SS34,D_SMA,SMD
25,"D3,D4",2,Diodes Inc,B5819W,B5819W,D_SOD-123,SMD
26,U5,1,Advanced Monolithic,AMS1117-3.3,AMS1117-3.3,SOT-223-3_TabPin2,SMD
27,"C15,C18,C22",3,,,10uF,C_0805_2012Metric,SMD
28,C16,1,,,22uF,C_0805_2012Metric,SMD
29,R8,1,,,1k,R_0603_1608Metric,SMD
30,D5,1,,,PWR green,LED_0603_1608Metric,SMD
31,U1,1,Espressif,ESP32-WROOM-32E-N4,ESP32-WROOM-32E (Drive),ESP32-WROOM-32E,SMD
32,"C20,C24",2,,,1uF,C_0603_1608Metric,SMD
33,J3,1,Korean Hroparts,TYPE-C-31-M-12,USB-C Drive,USB_C_Receptacle_HRO_TYPE-C-31-M-12,SMD
34,"R11,R12,R18,R19",4,,,5.1k,R_0603_1608Metric,SMD
35,"U10,U11",2,STMicroelectronics,USBLC6-2SC6,USBLC6-2SC6,SOT-23-6,SMD
36,"U6,U7",2,WCH,CH340C,CH340C,SOIC-16_3.9x9.9mm_P1.27mm,SMD
37,"R13,R20",2,,,0,R_0603_1608Metric,SMD
38,"Q3,Q4,Q5,Q6",4,onsemi,MMBT3904,MMBT3904,SOT-23,SMD
39,U2,1,Espressif,ESP32-WROOM-32E-N4,ESP32-WROOM-32E (Telemetry),ESP32-WROOM-32E,SMD
40,J4,1,Korean Hroparts,TYPE-C-31-M-12,USB-C Telemetry,USB_C_Receptacle_HRO_TYPE-C-31-M-12,SMD
41,U8,1,Texas Instruments,SN65HVD230DR,SN65HVD230 (A),SOIC-8_3.9x4.9mm_P1.27mm,SMD
42,U9,1,Texas Instruments,SN65HVD230DR,SN65HVD230 (B),SOIC-8_3.9x4.9mm_P1.27mm,SMD
43,JP1,1,,,TERM,SolderJumper-2_P1.3mm_Bridged_RoundedPad1.0x1.5mm,SMD
44,"R23,R24",2,,,60.4,R_0603_1608Metric,SMD
45,D6,1,Nexperia,"PESD2CAN,215",PESD2CAN,SOT-23,SMD
46,J5,1,JST,B3B-XH-A,CAN to Pi,JST_XH_B3B-XH-A_1x03_P2.50mm_Vertical,THT
47,J6,1,,,BTS7960,PinHeader_1x08_P2.54mm_Vertical,THT
48,J7,1,,,SERVO,PinHeader_1x03_P2.54mm_Vertical,THT
49,R28,1,,,100,R_0603_1608Metric,SMD
50,C29,1,,,470uF 10V,CP_Elec_8x10,SMD
51,R29,1,,,100k,R_0603_1608Metric,SMD
52,R30,1,,,33k,R_0603_1608Metric,SMD
53,J8,1,,,LCD ILI9488 3.5in,PinSocket_1x14_P2.54mm_Vertical,THT
54,Q7,1,Alpha & Omega,AO3401A,AO3401A,SOT-23,SMD

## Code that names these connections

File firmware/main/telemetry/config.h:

// ========================================
// TELEMETRY NODE CONFIGURATION
// ========================================

#pragma once

#include "sdkconfig.h"


// ---------- Pins ----------

#define PIN_CAN_TX              CONFIG_CAN_TWAI_TX_GPIO     // set in menuconfig
#define PIN_CAN_RX              CONFIG_CAN_TWAI_RX_GPIO
#define PIN_BATTERY_SENSE       34      // ADC1, input-only pin

// 3.5" ILI9488 display + XPT2046 touch, sharing one SPI bus
#define PIN_SPI_SCK             18
#define PIN_SPI_MOSI            23
#define PIN_SPI_MISO            19      // touch only: the ILI9488 never releases MISO
#define PIN_LCD_CS              13
#define PIN_LCD_DC              21
#define PIN_LCD_RST             22
#define PIN_LCD_BACKLIGHT       32      // drives a P-MOSFET on the mainboard: low = on
#define PIN_TOUCH_CS            14      // held high (touch isn't used yet)
#define PIN_TOUCH_IRQ           35

#define LCD_SPI_HZ              26000000


// ---------- Battery ----------
//
// Pack -> R_TOP -> ADC pin -> R_BOTTOM -> GND
// 100k / 33k turns a 2S pack's 8.4 V into ~2.1 V at the pin.

#define BATTERY_CELLS           2       // LiPo cells in series
#define DIVIDER_R_TOP_OHMS      100000
#define DIVIDER_R_BOTTOM_OHMS   33000

#define CELL_LOW_MV             3500    // warn
#define CELL_CRITICAL_MV        3300    // limit throttle (latched until reboot)
#define CELL_HYSTERESIS_MV      100

// Below this the node is assumed to be on USB power with no pack attached
#define NO_BATTERY_MV           2000


// ---------- Timing ----------

#define LOOP_PERIOD_MS          50      // CAN polling
#define BATTERY_PERIOD_MS       200     // 5 Hz battery message
#define SCREEN_PERIOD_MS        200     // 5 Hz display refresh
